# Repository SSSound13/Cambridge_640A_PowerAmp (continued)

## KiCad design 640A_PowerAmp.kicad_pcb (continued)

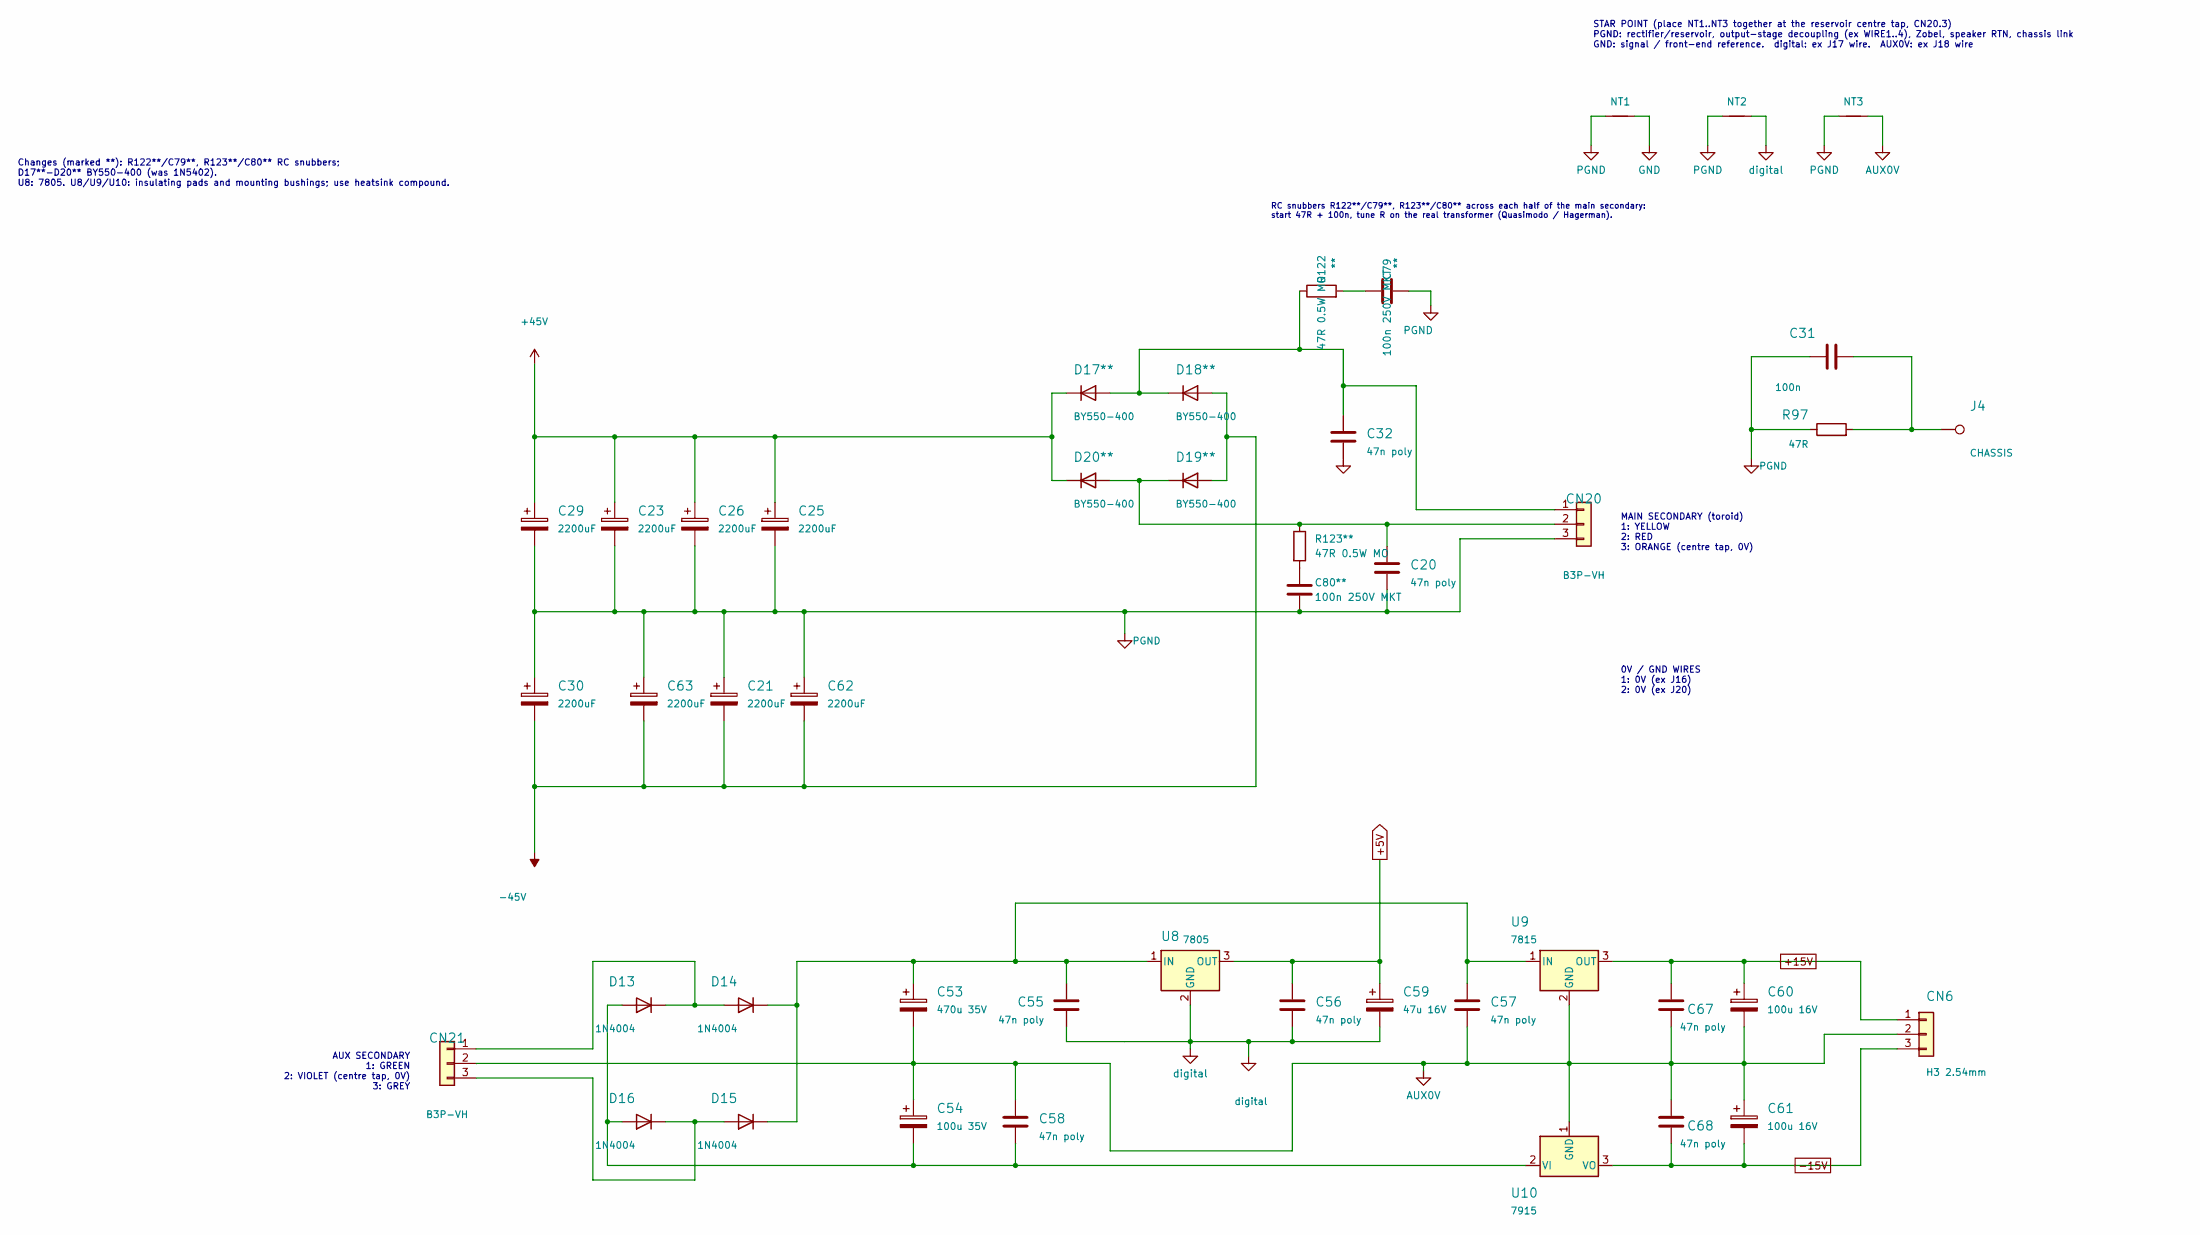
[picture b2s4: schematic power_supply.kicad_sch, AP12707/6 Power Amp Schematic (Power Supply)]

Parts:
C20, C32, C55, C56, C57, C58, C67, C68: 47n poly; C_Rect_L7.2mm_W2.5mm_P5.00mm_FKS2_FKP2_MKS2_MKP2
C21, C23, C25, C26, C29, C30, C62, C63: 2200uF; CP_Radial_D18.0mm_P7.50mm
C31: 100n; C_Disc_D7.5mm_W2.5mm_P5.00mm
C53: 470u 35V; CP_Radial_D10.0mm_P5.00mm
C54: 100u 35V; CP_Radial_D8.0mm_P3.50mm
C59: 47u 16V; CP_Radial_D5.0mm_P2.50mm
C60, C61: 100u 16V; CP_Radial_D5.0mm_P2.50mm
C79, C80: 100n 250V MKT; C_Rect_L9.0mm_W3.2mm_P7.50mm_MKT; MPN B32560J3104K000
CN6: H3 2.54mm; JST_XH_B3B-XH-A_1x03_P2.50mm_Vertical
CN20, CN21: B3P-VH; JST_VH_B3P-VH_1x03_P3.96mm_Vertical; MPN B3P-VH
D13, D14, D15, D16: 1N4004; D_DO-41_SOD81_P10.16mm_Horizontal
D17, D18, D19, D20: BY550-400; D_DO-201AD_P13.97mm_Horizontal; MPN BY550-400
J4: CHASSIS; TestPoint_THTPad_3.0x3.0mm_Drill1.5mm
NT1: NetTie_2; NetTie-2_THT_Star
NT2, NT3: NetTie_2; NetTie-2_THT_Pad1.0mm
R97: 47R; R_Axial_DIN0207_L6.3mm_D2.5mm_P10.16mm_Horizontal
R122, R123: 47R 0.5W MO; R_Axial_DIN0207_L6.3mm_D2.5mm_P10.16mm_Horizontal; MPN MO-50 0.5W 47R 5%
U8: 7805; TO-220-3_Vertical
U9: 7815; TO-220-3_Vertical
U10: 7915; TO-220-3_Vertical

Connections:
+5V: C56.1, C59.1, U8.3 (OUT); also elsewhere on the board
+15V: C60.1, C67.1, CN6.1, U9.3 (OUT); also elsewhere on the board
+45V: C23.1, C25.1, C26.1, C29.1, D17.1 (K), D20.1 (K); also elsewhere on the board
-15V: C61.2, C68.2, CN6.3, U10.3 (VO); also elsewhere on the board
-45V: C21.2, C30.2, C62.2, C63.2, D18.2 (A), D19.2 (A); also elsewhere on the board
AUX0V: C53.2, C54.1, C57.2, C58.1, C60.2, C61.1, C67.2, C68.1, CN6.2, CN21.2, NT3.2, U9.2 (GND), U10.1 (GND)
GND: NT1.2; also elsewhere on the board
unnamed: C31.2, J4.1 (1_1), R97.2
unnamed: C79.1, R122.2
unnamed: C80.1, R123.2
unnamed: C32.1, CN20.1, D17.2 (A), D18.1 (K), R122.1
unnamed: C20.1, CN20.2, D19.1 (K), D20.2 (A), R123.1
unnamed: CN21.1, D13.1 (K), D14.2 (A)
unnamed: CN21.3, D15.2 (A), D16.1 (K)
unnamed: C54.2, C58.2, D13.2 (A), D16.2 (A), U10.2 (VI)
unnamed: C53.1, C55.1, C57.1, D14.1 (K), D15.1 (K), U8.1 (IN), U9.1 (IN)
PGND: C20.2, C21.1, C23.2, C25.2, C26.2, C29.2, C30.1, C31.1, C32.2, C62.1, C63.1, C79.2, C80.2, CN20.3, NT1.1, NT2.1, NT3.1, R97.1; also elsewhere on the board
digital: C55.2, C56.2, C59.2, NT2.2, U8.2 (GND); also elsewhere on the board

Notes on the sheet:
AUX SECONDARY 1: GREEN 2: VIOLET (centre tap, 0V) 3: GREY
STAR POINT (place NT1..NT3 together at the reservoir centre tap, CN20.3) PGND: rectifier/reservoir, output-stage decoupling (ex WIRE1..4), Zobel, speaker RTN, chassis link GND: signal / front-end reference. digital: ex J17 wire. AUX0V: ex J18 wire
RC snubbers R122**/C79**, R123**/C80** across each half of the main secondary: start 47R + 100n, tune R on the real transformer (Quasimodo / Hagerman).
MAIN SECONDARY (toroid) 1: YELLOW 2: RED 3: ORANGE (centre tap, 0V)
0V / GND WIRES 1: 0V (ex J16) 2: 0V (ex J20)
Changes (marked **): R122**/C79**, R123**/C80** RC snubbers; D17**-D20** BY550-400 (was 1N5402). U8: 7805. U8/U9/U10: insulating pads and mounting bushings; use heatsink compound.

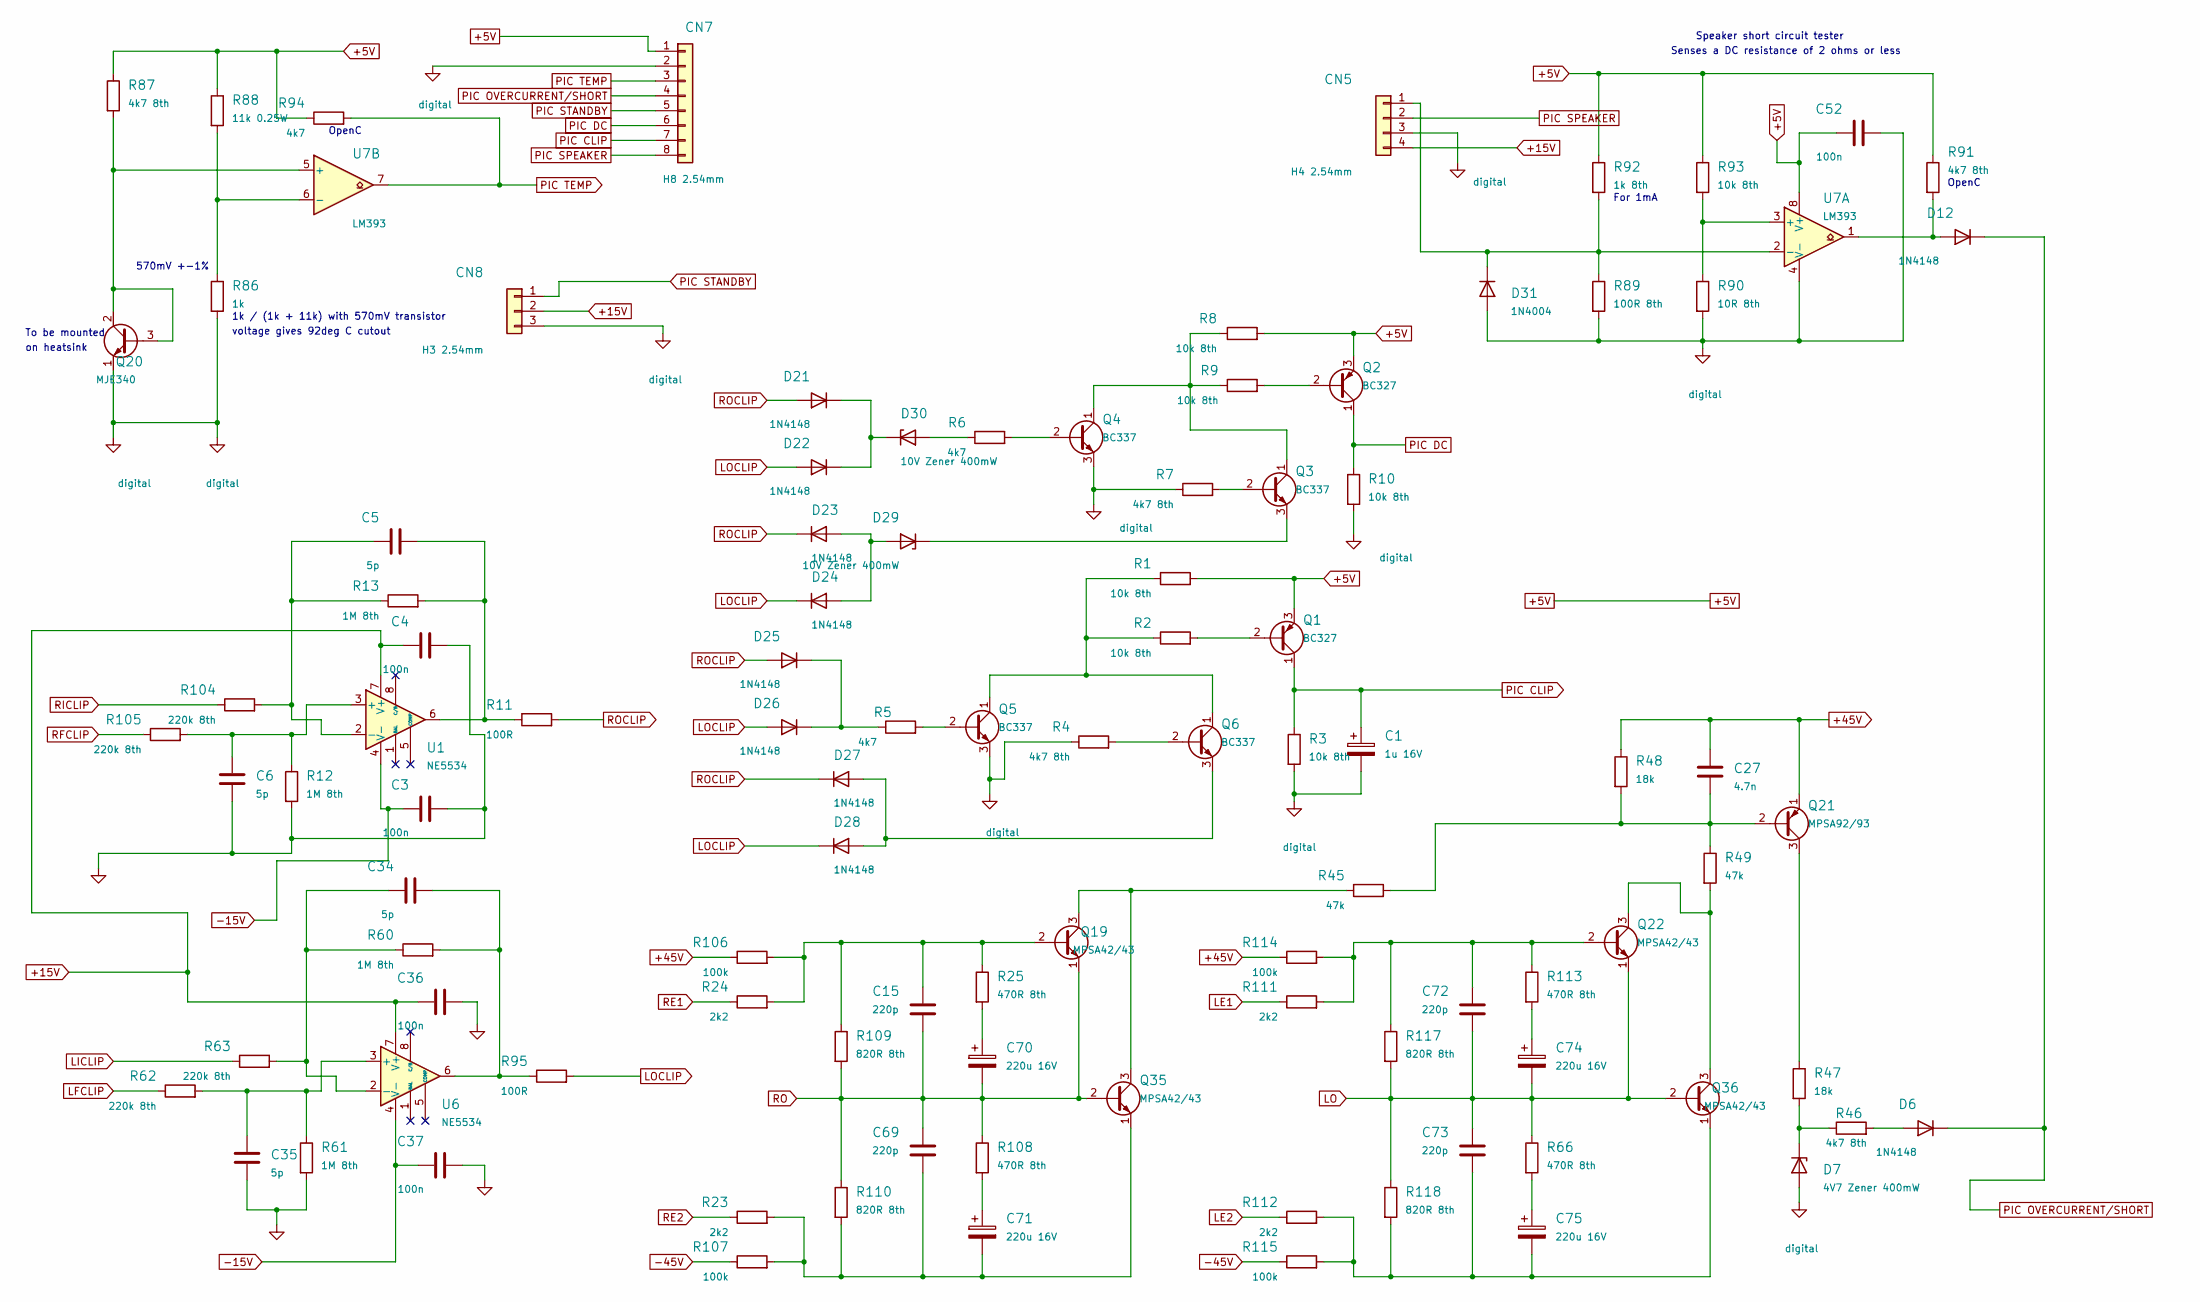
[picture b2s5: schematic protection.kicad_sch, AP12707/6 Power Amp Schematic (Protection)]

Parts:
C1: 1u 16V; CP_Radial_D5.0mm_P2.50mm
C3, C4, C36, C37, C52: 100n; C_Disc_D7.5mm_W2.5mm_P5.00mm
C5, C6, C34, C35: 5p; C_Disc_D5.0mm_W2.5mm_P5.00mm
C15, C69, C72, C73: 220p; C_Disc_D5.0mm_W2.5mm_P5.00mm
C27: 4.7n; C_Disc_D7.5mm_W2.5mm_P5.00mm
C70, C71, C74, C75: 220u 16V; CP_Radial_D10.0mm_P5.00mm
CN5: H4 2.54mm; JST_XH_B4B-XH-A_1x04_P2.50mm_Vertical
CN7: H8 2.54mm; JST_XH_B8B-XH-A_1x08_P2.50mm_Vertical
CN8: H3 2.54mm; JST_XH_B3B-XH-A_1x03_P2.50mm_Vertical
D6, D12, D21, D22, D23, D24, D25, D26, D27, D28: 1N4148; D_DO-35_SOD27_P7.62mm_Horizontal
D7: 4V7 Zener 400mW; D_DO-35_SOD27_P7.62mm_Horizontal
D29, D30: 10V Zener 400mW; D_DO-35_SOD27_P7.62mm_Horizontal
D31: 1N4004; D_DO-41_SOD81_P10.16mm_Horizontal
Q1, Q2: BC327; TO-92_Inline_Wide
Q3, Q4, Q5, Q6: BC337; TO-92_Inline_Wide
Q19, Q22, Q35, Q36: MPSA42/43; TO-92_Inline_Wide
Q20: MJE340; TO-126-3_Vertical
Q21: MPSA92/93; TO-92_Inline_Wide
R1, R2, R3, R8, R9, R10, R93: 10k 8th; R_Axial_DIN0204_L3.6mm_D1.6mm_P7.62mm_Horizontal
R4, R7, R87, R91: 4k7 8th; R_Axial_DIN0204_L3.6mm_D1.6mm_P7.62mm_Horizontal
R5, R6, R94: 4k7; R_Axial_DIN0207_L6.3mm_D2.5mm_P10.16mm_Horizontal
R11, R95: 100R; R_Axial_DIN0207_L6.3mm_D2.5mm_P10.16mm_Horizontal
R12, R13, R60, R61: 1M 8th; R_Axial_DIN0204_L3.6mm_D1.6mm_P7.62mm_Horizontal
R23, R24, R111, R112: 2k2; R_Axial_DIN0207_L6.3mm_D2.5mm_P10.16mm_Horizontal
R25, R66, R108, R113: 470R 8th; R_Axial_DIN0204_L3.6mm_D1.6mm_P7.62mm_Horizontal
R45, R49: 47k; R_Axial_DIN0207_L6.3mm_D2.5mm_P10.16mm_Horizontal
R46: 4k7 8th; R_Axial_DIN0207_L6.3mm_D2.5mm_P10.16mm_Horizontal
R47, R48: 18k; R_Axial_DIN0207_L6.3mm_D2.5mm_P10.16mm_Horizontal
R62, R63, R104, R105: 220k 8th; R_Axial_DIN0204_L3.6mm_D1.6mm_P7.62mm_Horizontal
R86: 1k; R_Axial_DIN0207_L6.3mm_D2.5mm_P10.16mm_Horizontal
R88: 11k 0.25W; R_Axial_DIN0204_L3.6mm_D1.6mm_P7.62mm_Horizontal
R89: 100R 8th; R_Axial_DIN0204_L3.6mm_D1.6mm_P7.62mm_Horizontal
R90: 10R 8th; R_Axial_DIN0204_L3.6mm_D1.6mm_P7.62mm_Horizontal
R92: 1k 8th; R_Axial_DIN0204_L3.6mm_D1.6mm_P7.62mm_Horizontal
R106, R107, R114, R115: 100k; R_Axial_DIN0207_L6.3mm_D2.5mm_P10.16mm_Horizontal
R109, R110, R117, R118: 820R 8th; R_Axial_DIN0204_L3.6mm_D1.6mm_P7.62mm_Horizontal
U1, U6: NE5534; DIP-8_W7.62mm
U7: LM393; DIP-8_W7.62mm

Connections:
+5V: C52.1, CN7.1, Q1.3 (E), Q2.3 (E), R1.2, R8.2, R87.1, R88.1, R91.1, R92.1, R93.1, R94.1, U7.8 (V+); also elsewhere on the board
+15V: C4.1, C36.1, CN5.4, CN8.2, U1.7 (V+), U6.7 (V+); also elsewhere on the board
+45V: C27.1, Q21.1 (E), R48.1, R106.1, R114.1; also elsewhere on the board
-15V: C3.1, C37.1, U1.4 (V-), U6.4 (V-); also elsewhere on the board
-45V: R107.1, R115.1; also elsewhere on the board
GND: C3.2, C4.2, C6.2, C35.2, C36.2, C37.2, R12.2, R61.2; also elsewhere on the board
LE1: R111.1; also elsewhere on the board
LE2: R112.1; also elsewhere on the board
LFCLIP: R62.1; also elsewhere on the board
LICLIP: R63.1; also elsewhere on the board
LO: C72.2, C73.1, C74.2, Q22.1 (E), Q36.2 (B), R66.1, R117.2, R118.1; also elsewhere on the board
LOCLIP: D22.2 (A), D24.1 (K), D26.2 (A), D28.1 (K), R95.2
unnamed: C5.2, R11.1, R13.2, U1.6
unnamed: C34.2, R60.2, R95.1, U6.6
unnamed: C70.1, R25.2
unnamed: C71.1, R108.2
unnamed: C74.1, R113.2
unnamed: C75.1, R66.2
unnamed: CN5.1, D31.1 (K), R89.1, R92.2, U7.2 (-)
unnamed: D6.2 (A), R46.2
unnamed: D7.1 (K), R46.1, R47.2
unnamed: D12.2 (A), R91.2, U7.1
unnamed: D21.1 (K), D22.1 (K), D30.1 (K)
unnamed: D23.2 (A), D24.2 (A), D29.2 (A)
unnamed: D25.1 (K), D26.1 (K), R5.1
unnamed: D27.2 (A), D28.2 (A), Q6.3 (E)
unnamed: D29.1 (K), Q3.3 (E)
unnamed: D30.2 (A), R6.1
unnamed: Q1.2 (B), R2.2
unnamed: Q2.2 (B), R9.2
unnamed: Q3.2 (B), R7.2
unnamed: Q3.1 (C), Q4.1 (C), R8.1, R9.1
unnamed: Q4.2 (B), R6.2
unnamed: Q5.2 (B), R5.2
unnamed: Q5.1 (C), Q6.1 (C), R1.1, R2.1
unnamed: Q6.2 (B), R4.2
unnamed: C15.1, Q19.2 (B), R24.2, R25.1, R106.2, R109.1
unnamed: Q19.3 (C), Q35.3 (C), R45.1
unnamed: Q20.2 (C), Q20.3 (B), R87.2, U7.5 (+)
unnamed: C27.2, Q21.2 (B), R45.2, R48.2, R49.1
unnamed: Q21.3 (C), R47.1
unnamed: C72.1, Q22.2 (B), R111.2, R113.1, R114.2, R117.1
unnamed: Q22.3 (C), Q36.3 (C), R49.2
unnamed: C69.2, C71.2, Q35.1 (E), R23.2, R107.2, R110.2
unnamed: C73.2, C75.2, Q36.1 (E), R112.2, R115.2, R118.2
unnamed: C6.1, R12.1, R105.2, U1.3 (+)
unnamed: C5.1, R13.1, R104.2, U1.2 (-)
unnamed: C35.1, R61.1, R62.2, U6.3 (+)
unnamed: C34.1, R60.1, R63.2, U6.2 (-)
unnamed: R90.1, R93.2, U7.3 (+)
unnamed: R86.1, R88.2, U7.6 (-)
PIC CLIP: C1.1, CN7.7, Q1.1 (C), R3.1
PIC DC: CN7.6, Q2.1 (C), R10.1
PIC OVERCURRENT/SHORT: CN7.4, D6.1 (K), D12.1 (K)
PIC SPEAKER: CN5.2, CN7.8
PIC STANDBY: CN7.5, CN8.1
PIC TEMP: CN7.3, R94.2, U7.7
RE1: R24.1; also elsewhere on the board
RE2: R23.1; also elsewhere on the board
RFCLIP: R105.1; also elsewhere on the board
RICLIP: R104.1; also elsewhere on the board
RO: C15.2, C69.1, C70.2, Q19.1 (E), Q35.2 (B), R108.1, R109.2, R110.1; also elsewhere on the board
ROCLIP: D21.2 (A), D23.1 (K), D25.2 (A), D27.1 (K), R11.2
digital: C1.2, C52.2, CN5.3, CN7.2, CN8.3, D7.2 (A), D31.2 (A), Q4.3 (E), Q5.3 (E), Q20.1 (E), R3.2, R4.1, R7.1, R10.2, R86.2, R89.2, R90.2, U7.4 (V-); also elsewhere on the board

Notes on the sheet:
570mV +-1%
For 1mA
OpenC
Senses a DC resistance of 2 ohms or less
To be mounted
Speaker short circuit tester
on heatsink
voltage gives 92deg C cutout
1k / (1k + 11k) with 570mV transistor

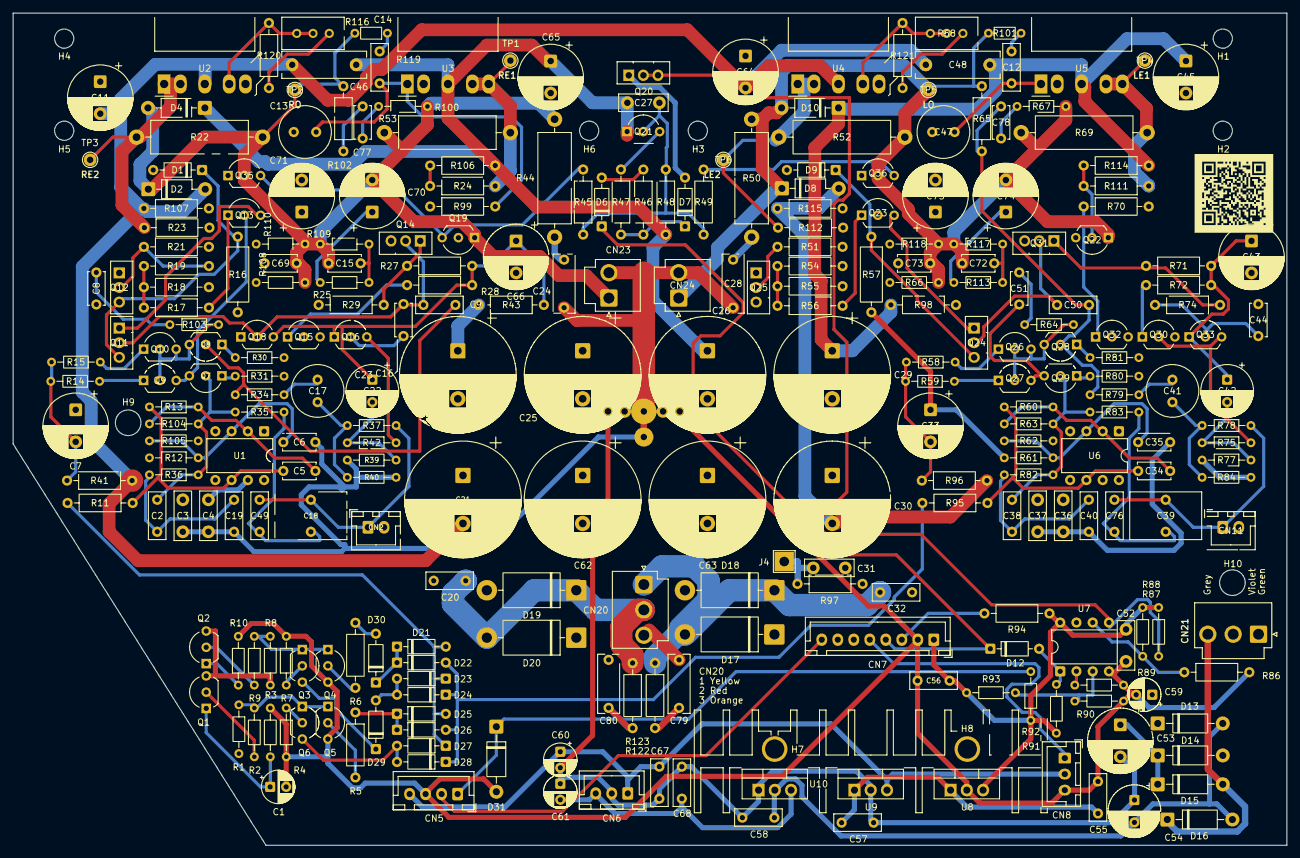
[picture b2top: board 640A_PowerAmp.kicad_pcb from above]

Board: 4 copper layers, 198.9 x 130.0 mm, 296 parts (0 on the bottom side), 141 nets.

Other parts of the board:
H1, H2, H3, H4, H5, H6: bracket fixing, 3.0 mm NPTH; MountingHole_NPTH_3.0mm
H7: heatsink pin, 3.0 mm PTH; MountingHole_PTH_3.0mm_Pad4.0mm
H8: heatsink pin, 3.0 mm PTH; no separate digital tra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; MountingHole_PTH_3.0mm_Pad4.0mm
H9, H10: standoff, 4.0 mm NPTH; MountingHole_NPTH_4.0mm

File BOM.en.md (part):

# Bill of materials — current Cambridge 640A revision

[Русский](BOM.md) · [Project overview](README.en.md) · [Source CSV, Russian](BOM.csv) · [Excel, Russian](BOM.xlsx)

Generated from the same authoritative BOM.csv. **+ means added relative to the factory board**; replacements and larger footprints are not marked as additions. The PCB has 283 positions: 274 fitted components, 2 DNP positions and 7 pads without purchased parts. NT1–NT3 are board copper. Mating connector parts are counted separately.

R88 is 1/4 W; R53/R64/R67/R103 are 1/8 W per the factory BOM, page 23. R68/R116 are 47 ohm, 0.5 W trimmers. All footprint dimensions correspond to the current PCB.

| Category | Group | Qty | References | Value | Power, W | Package / footprint | Manufacturer and part number | + | Notes |
| --- | --- | --- | --- | --- | --- | --- | --- | --- | --- |
| Resistors | 1/8 W | 3 | R40, R84, R90 | 10 ohm | 0.125 | DIN0204, pitch 7.62 |  |  | 1%, metal film. |
| Resistors | 1/8 W | 4 | R14, R15, R58, R59 | 47 ohm | 0.125 | DIN0204, pitch 7.62 |  |  | 1%, metal film. |
| Resistors | 1/8 W | 2 | R101, R119 | 47 ohm | 0.125 | DIN0204, pitch 5.08 |  |  | 1%, metal film. |
| Resistors | 1/8 W | 5 | R30, R31, R80, R81, R89 | 100 ohm | 0.125 | DIN0204, pitch 7.62 |  |  | 1%, metal film. |
| Resistors | 1/8 W | 4 | R53, R64, R67, R103 | 150 ohm | 0.125 | DIN0204, pitch 7.62 |  |  | 1%, metal film; factory BOM, page 23. |
| Resistors | 1/8 W | 4 | R25, R66, R108, R113 | 470 ohm | 0.125 | DIN0204, pitch 7.62 |  |  | 1%, metal film. |
| Resistors | 1/8 W | 4 | R109, R110, R117, R118 | 820 ohm | 0.125 | DIN0204, pitch 7.62 |  |  | 1%, metal film. |
| Resistors | 1/8 W | 3 | R34, R79, R92 | 1 kohm | 0.125 | DIN0204, pitch 7.62 |  |  | 1%, metal film. |
| Resistors | 1/8 W | 6 | R4, R7, R35, R83, R87, R91 | 4.7 kohm | 0.125 | DIN0204, pitch 7.62 |  |  | 1%, metal film. |
| Resistors | 1/8 W | 1 | R46 | 4.7 kohm | 0.125 | DIN0207, pitch 10.16 |  |  | 1%, metal film. |
| Resistors | 1/8 W | 11 | R1, R2, R3, R8, R9, R10, R39, R42, R75, R77, R93 | 10 kohm | 0.125 | DIN0204, pitch 7.62 |  |  | 1%, metal film. |
| Resistors | 1/8 W | 2 | R36, R82 | 33 kohm | 0.125 | DIN0204, pitch 7.62 |  |  | 1%, metal film. |
| Resistors | 1/8 W | 4 | R62, R63, R104, R105 | 220 kohm | 0.125 | DIN0204, pitch 7.62 |  |  | 1%, metal film. |
| Resistors | 1/8 W | 2 | R37, R78 | 330 kohm | 0.125 | DIN0204, pitch 7.62 |  |  | 1%, metal film. |
| Resistors | 1/8 W | 4 | R12, R13, R60, R61 | 1 Mohm | 0.125 | DIN0204, pitch 7.62 |  |  | 1%, metal film. |
| Resistors | 1/4 W | 1 | R97 | 47 ohm | 0.25 | DIN0207, pitch 10.16 |  |  | 1%, metal film. |
| Resistors | 1/4 W | 8 | R11, R17, R21, R51, R56, R70, R95, R99 | 100 ohm | 0.25 | DIN0207, pitch 10.16 |  |  | 1%, metal film. |
| Resistors | 1/4 W | 2 | R120, R121 | 100 ohm | 0.25 | DIN0204 vertical | MF-25 0.25W 100R 1% | + | 1%. Added to limit bias-adjustment resistance. |
| Resistors | 1/4 W | 4 | R27, R28, R71, R72 | 150 ohm | 0.25 | DIN0207, pitch 10.16 |  |  | 1%, metal film. |
| Resistors | 1/4 W | 5 | R18, R29, R55, R74, R86 | 1 kohm | 0.25 | DIN0207, pitch 10.16 |  |  | 1%, metal film. |
| Resistors | 1/4 W | 4 | R23, R24, R111, R112 | 2.2 kohm | 0.25 | DIN0207, pitch 10.16 |  |  | 1%, metal film. |
| Resistors | 1/4 W | 3 | R5, R6, R94 | 4.7 kohm | 0.25 | DIN0207, pitch 10.16 |  |  | 1%, metal film. |
| Resistors | 1/4 W | 1 | R88 | 11 kohm | 0.25 | DIN0204, pitch 7.62 |  |  | 1%, metal film; 1/4 W per factory BOM. |
| Resistors | 1/4 W | 4 | R19, R47, R48, R54 | 18 kohm | 0.25 | DIN0207, pitch 10.16 |  |  | 1%, metal film. |
| Resistors | 1/4 W | 2 | R65, R102 | 33 kohm | 0.25 | DIN0207, pitch 10.16 |  |  | 1%, metal film. |
| Resistors | 1/4 W | 2 | R45, R49 | 47 kohm | 0.25 | DIN0207, pitch 10.16 |  |  | 1%, metal film. |
| Resistors | 1/4 W | 4 | R106, R107, R114, R115 | 100 kohm | 0.25 | DIN0207, pitch 10.16 |  |  | 1%, metal film. |
| Resistors | 1/2 W | 2 | R122, R123 | 47 ohm | 0.5 | DIN0207 horizontal, pitch 10.16 (revised v2) | MO-50 0.5W 47R 5% | + | Added snubbers; 47 ohm is the initial value, adjusted by secondary-winding ringing measurements. |
| Resistors | 1/2 W | 4 | R41, R43, R96, R98 | 150 ohm | 0.5 | DIN0207, pitch 10.16 | TE Connectivity (Neohm) FRN50J150R/S |  | Flameproof fusible, 150 ohm / 0.5 W. Replacement for factory part. |
| Resistors | 0.66 W | 2 | R16, R57 | 8.2 kohm | 0.66 | DIN0309, pitch 11.81 |  |  |  |
| Resistors | 3 W | 4 | R22, R52, R69, R100 | 0.22 ohm | 3 | DIN0516, pitch 19.69 |  |  | Wirewound. |
| Resistors | 3 W | 2 | R44, R50 | 4.7 ohm | 3 | DIN0516, pitch 18.42 | Vishay AC03000004708JAC00 |  | Wirewound; mount about 3 mm above PCB. |
| Resistors | Trimmers | 2 | R68, R116 | 47 ohm | 0.5 | Bourns 3296W |  |  | Bias trimmer. |
| Capacitors | Ceramic | 4 | C5, C6, C34, C35 | 5p |  | disc Ø5, pitch 5 |  |  |  |
| Capacitors | Ceramic | 2 | C16, C44 | 5p |  | disc Ø5, pitch 5 |  |  | DNP — do not fit; compensation positions reserved in case of oscillation. |
| Capacitors | Ceramic | 2 | C77, C78 | 22p |  | disc Ø5, pitch 5 |  |  |  |
| Capacitors | Ceramic | 2 | C9, C50 | 33p |  | 7.2×2.5 mm, pitch 5 |  |  |  |
| Capacitors | Ceramic | 4 | C15, C69, C72, C73 | 220p |  | disc Ø5, pitch 5 |  |  |  |
| Capacitors | Ceramic | 2 | C8, C51 | 470p |  | disc Ø5, pitch 5 |  |  |  |
| Capacitors | Ceramic | 1 | C27 | 4.7n |  | disc Ø7.5, pitch 5 |  |  |  |
| Capacitors | Ceramic | 6 | C3, C4, C31, C36, C37, C52 | 100n |  | disc Ø7.5, pitch 5 |  |  |  |
| Capacitors | Film | 2 | C2, C38 | 100p poly |  | 7.2×2.5 mm, pitch 5 |  |  |  |
| Capacitors | Film | 2 | C49, C76 | 2.2n PPE Bypass (640A only) |  | 7.2×2.5 mm, pitch 5 |  |  |  |
| Capacitors | Film | 2 | C12, C14 | 15n poly |  | 7.2×2.5 mm, pitch 5 |  |  |  |
| Capacitors | Film | 10 | C19, C20, C32, C40, C55, C56, C57, C58, C67, C68 | 47n poly |  | 7.2×2.5 mm, pitch 5 |  |  |  |
| Capacitors | Film | 2 | C24, C28 | 100n 250V MKT |  | 9×3.2 mm, pitch 7.5 | TDK (EPCOS) B32560J3104K000 |  | Replacement for factory Zobel capacitors. |
| Capacitors | Film | 2 | C46, C48 | 100n 160V Poly |  | 13×4 mm, pitch 10 |  |  |  |
| Capacitors | Film | 2 | C79, C80 | 100n 250V MKT |  | 9×3.2 mm, pitch 7.5 | TDK (EPCOS) B32560J3104K000 | + | Added: secondary-winding RC snubber capacitors. |
| Capacitors | Film | 2 | C18, C39 | 2u2 100V film (MKS2) |  | 7.2×11 mm, pitch 5 | WIMA MKS2D042201N00KO00 (MKS2-2.2U/100-R) |  | Replacement for the factory part. |
| Capacitors | Non-polar electrolytic | 2 | C13, C47 | 10u NP 16V |  | radial Ø8, pitch 3.5 |  |  | Enlarged footprint in current revision. |
| Capacitors | Non-polar electrolytic | 2 | C17, C41 | 220u NP 10V (D8) |  | radial Ø8, pitch 3.5 | Panasonic ECE-A1AN221U |  | Replacement for the factory part. |
| Capacitors | Electrolytic | 1 | C1 | 1u 16V |  | radial Ø5, pitch 2.5 |  |  |  |
| Capacitors | Electrolytic | 2 | C22, C42 | 47u 50V |  | radial Ø8, pitch 3.5 | UKL1H470KPD1TA |  | Footprint Ø8 mm, 3.5 mm pitch. |
| Capacitors | Electrolytic | 1 | C59 | 47u 16V |  | radial Ø5, pitch 2.5 |  |  |  |
| Capacitors | Electrolytic | 1 | C54 | 100u 35V |  | radial Ø8, pitch 3.5 |  |  |  |
| Capacitors | Electrolytic | 2 | C60, C61 | 100u 16V |  | radial Ø5, pitch 2.5 |  |  |  |
| Capacitors | Electrolytic | 8 | C7, C11, C33, C43, C45, C64, C65, C66 | 220u 50V |  | radial Ø10, pitch 5 |  |  | 63 V preferred for C7/C33/C43/C66. |
| Capacitors | Electrolytic | 4 | C70, C71, C74, C75 | 220u 16V |  | radial Ø10, pitch 5 |  |  | Choose the body and lead forming to match this footprint. |
| Capacitors | Electrolytic | 1 | C53 | 470u 35V |  | radial Ø10, pitch 5 |  |  |  |
| Capacitors | Electrolytic | 8 | C21, C23, C25, C26, C29, C30, C62, C63 | 2200 uF / 50 V |  | radial Ø18, pitch 7.5 |  |  |  |
| Diodes | Rectifier / signal | 4 | D2, D4, D8, D10 | 1N4004 |  | DO 41, pitch 8.89 |  |  |  |
| Diodes | Rectifier / signal | 10 | D6, D12, D21, D22, D23, D24, D25, D26, D27, D28 | 1N4148 |  | DO 35, pitch 7.62 |  |  |  |
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
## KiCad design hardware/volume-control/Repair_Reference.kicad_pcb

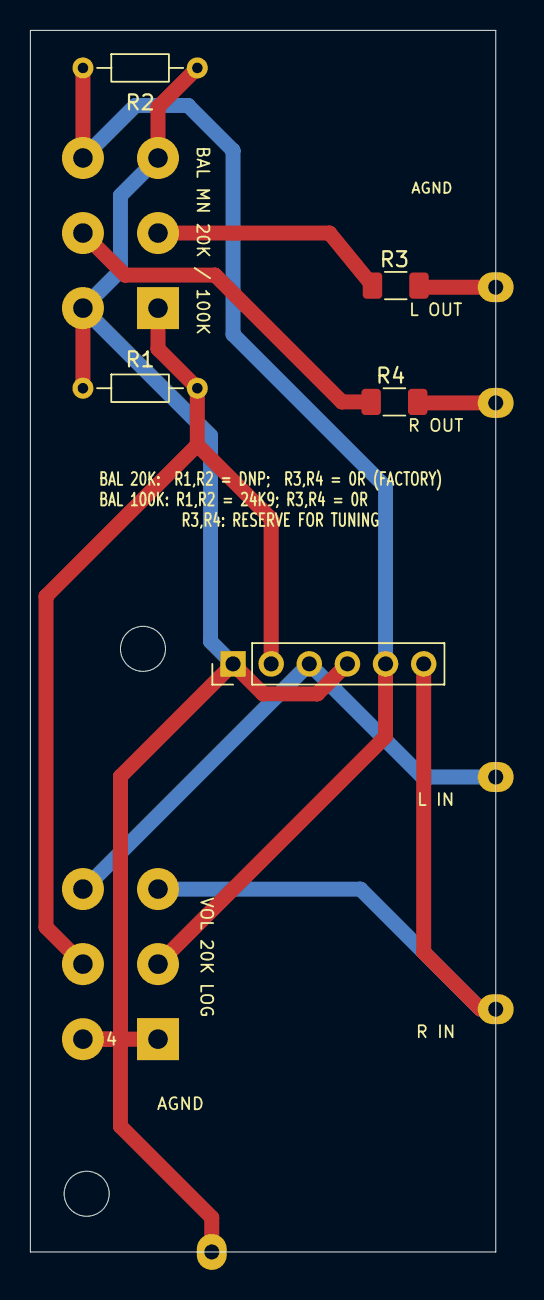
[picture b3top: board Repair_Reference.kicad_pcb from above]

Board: 2 copper layers, 31.0 x 81.4 mm, 14 parts (0 on the bottom side), 9 nets.

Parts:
H_ALPS1, H_ALPS2: MountingHole_3mm
J1: IN_R; Castellated_1.0mm
J2: IN_L; Castellated_1.0mm
J3: TO_BUF_R; Castellated_1.0mm
J4: TO_BUF_L; Castellated_1.0mm
J5: AGND; Castellated_1.0mm
J_ALPS: ALPS landing pads - routing pending; PinHeader_1x06_P2.54mm_Vertical
R1, R2: 24.9k 1/8W; R_Axial_DIN0204_L3.6mm_D1.6mm_P7.62mm_Horizontal
R3, R4: 0R; R_1206_3216Metric_Pad1.30x1.75mm_HandSolder
VR1: 20k LOG; VR1_RM16_6Pin_5mm_DRAFT
VR4: 100k MN; VR4_MN_6Pin_5mm_DRAFT

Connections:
/AGND: J5.1, J_ALPS.1, J_ALPS.4, R1.1, R2.2, VR1.1, VR1.4, VR4.3, VR4.4
/IN_L: J2.1, J_ALPS.3, VR1.6
/IN_R: J1.1, J_ALPS.6, VR1.3
/TO_BUF_L: J4.1, R3.2
/TO_BUF_R: J3.1, R4.2
/VOL_L: J_ALPS.2, R1.2, VR1.5, VR4.1
/VOL_R: J_ALPS.5, R2.1, VR1.2, VR4.6
/WIPER_L: R3.1, VR4.2
/WIPER_R: R4.1, VR4.5

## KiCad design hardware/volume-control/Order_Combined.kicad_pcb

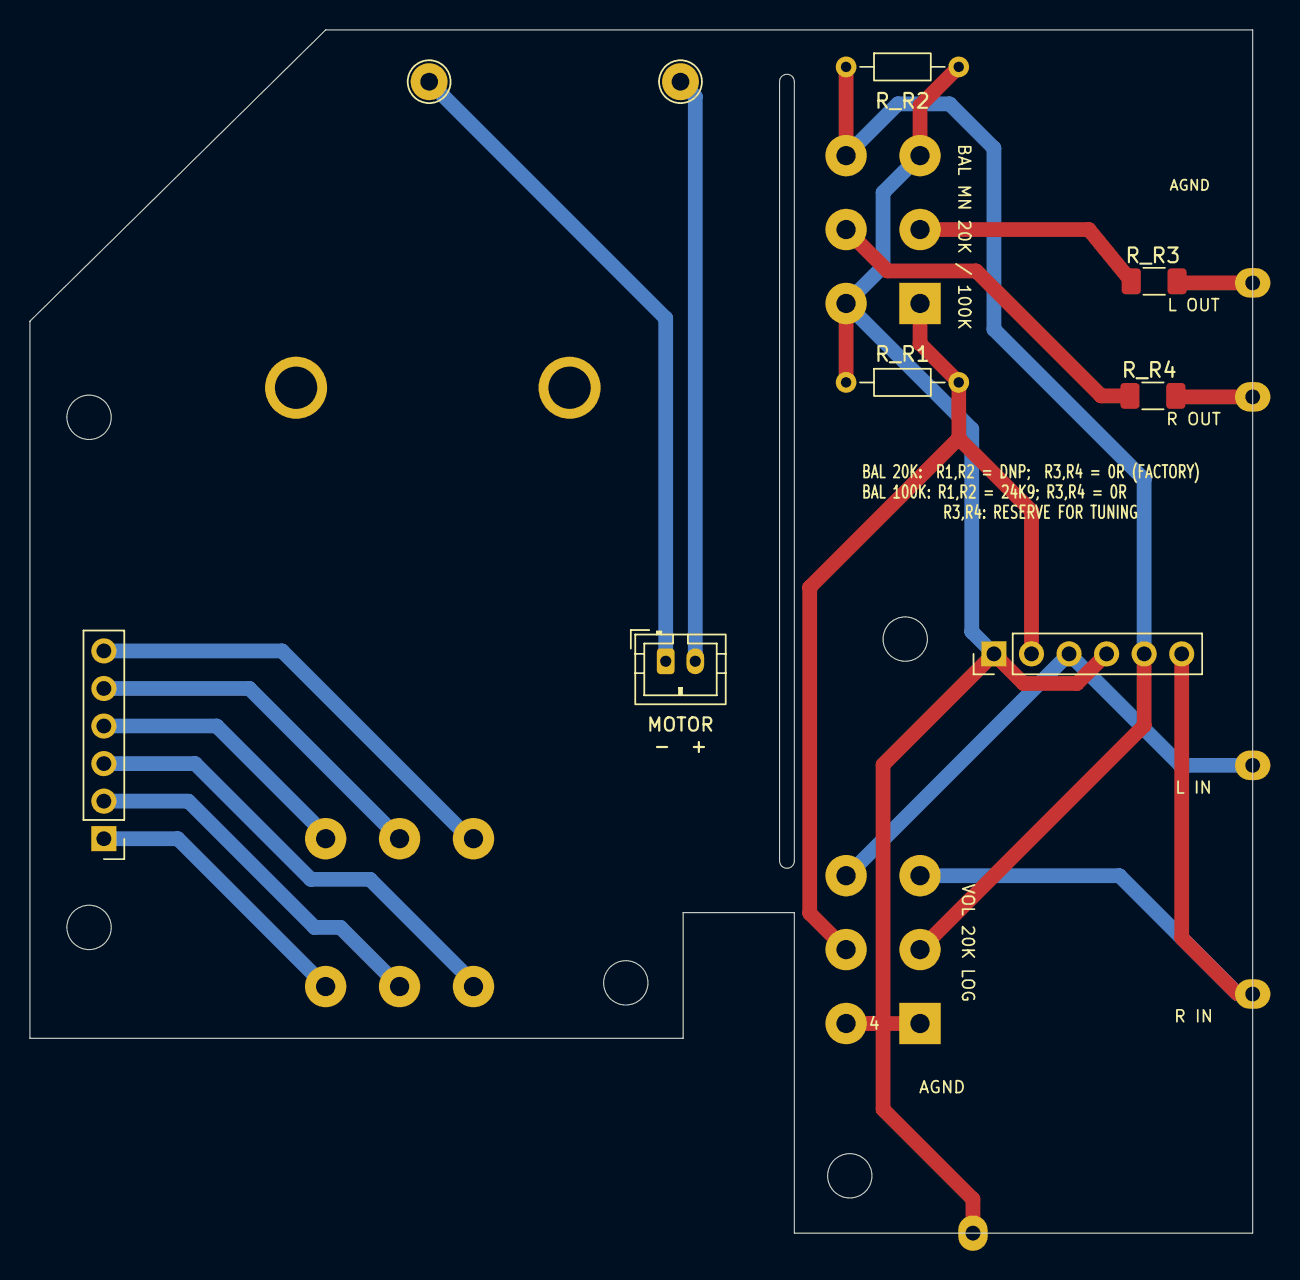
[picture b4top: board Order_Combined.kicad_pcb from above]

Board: 2 copper layers, 82.7 x 81.4 mm, 22 parts (0 on the bottom side), 17 nets.

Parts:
A_H1, A_H2, A_H3: MountingHole_3mm
A_J1: 1x06 / 2.54 mm; PinHeader_1x06_P2.54mm_Vertical
A_J2: B2B-PH-K-S; JST_PH_B2B-PH-K_1x02_P2.00mm_Vertical
A_MP1, A_MP2: Motor PCB terminal; TestPoint_THTPad_D2.5mm_Drill1.2mm
A_RV1: RK27112MC / value TBC; RK27112MC
R_H_ALPS1, R_H_ALPS2: MountingHole_3mm
R_J1: IN_R; Castellated_1.0mm
R_J2: IN_L; Castellated_1.0mm
R_J3: TO_BUF_R; Castellated_1.0mm
R_J4: TO_BUF_L; Castellated_1.0mm
R_J5: AGND; Castellated_1.0mm
R_J_ALPS: ALPS landing pads - routing pending; PinHeader_1x06_P2.54mm_Vertical
R_R1, R_R2: 24.9k 1/8W; R_Axial_DIN0204_L3.6mm_D1.6mm_P7.62mm_Horizontal
R_R3, R_R4: 0R; R_1206_3216Metric_Pad1.30x1.75mm_HandSolder
R_VR1: 20k LOG; VR1_RM16_6Pin_5mm_DRAFT
R_VR4: 100k MN; VR4_MN_6Pin_5mm_DRAFT

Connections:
A_/MOTOR_A: A_J2.1, A_MP1.1
A_/MOTOR_B: A_J2.2, A_MP2.1
A_/R1_HIGH: A_J1.3, A_RV1.3
A_/R1_LOW: A_J1.1, A_RV1.1
A_/R1_WIPER: A_J1.2, A_RV1.2
A_/R2_HIGH: A_J1.6, A_RV1.6
A_/R2_LOW: A_J1.4, A_RV1.4
A_/R2_WIPER: A_J1.5, A_RV1.5
R_/AGND: R_J5.1, R_J_ALPS.1, R_J_ALPS.4, R_R1.1, R_R2.2, R_VR1.1, R_VR1.4, R_VR4.3, R_VR4.4
R_/IN_L: R_J2.1, R_J_ALPS.3, R_VR1.6
R_/IN_R: R_J1.1, R_J_ALPS.6, R_VR1.3
R_/TO_BUF_L: R_J4.1, R_R3.2
R_/TO_BUF_R: R_J3.1, R_R4.2
R_/VOL_L: R_J_ALPS.2, R_R1.2, R_VR1.5, R_VR4.1
R_/VOL_R: R_J_ALPS.5, R_R2.1, R_VR1.2, R_VR4.6
R_/WIPER_L: R_R3.1, R_VR4.2
R_/WIPER_R: R_R4.1, R_VR4.5
